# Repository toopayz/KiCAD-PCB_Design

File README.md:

# KiCAD Collection
بِسْمِ اللَّهِ الرَّحْمَنِ الرَّحِيم... 
 
All my KiCAD Collection include Symbol, Footprint, 3D Models, and PCB project.  
Symbol, Footprint, and 3D model can change anytime without information.  
You can refer to "List Component & Board.xlsx" file for reference.

License : Don't Care License, Do what u want...^^...  
Information :
- OS   : Windows 10 64 bit  
- Software : KiCAD v7.0  

## Manage Symbol Libraries  

## Manage Footprint Libraries  

## Manage 3D Model  

//-------------- End Of ReadMe

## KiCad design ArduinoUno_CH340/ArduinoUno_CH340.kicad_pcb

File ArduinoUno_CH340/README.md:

# Arduino Uno R3
بِسْمِ اللَّهِ الرَّحْمَنِ الرَّحِيم... 
 
Create Schematic, PCBA, and 3D Step file based on Arduino Uno R3.  
This project purposes just for trial symbol, footprint, and 3D Model.  

License : Don't Care License, Do what u want...^^...  
Information :
- OS   : Windows 10 64 bit  
- Software : KiCAD v7.0  
- Status : Completed and will Not Continue.
- Date Complete : 20 June 2023

## Project  

## Schematic  

## PCB Board  

## Image  

//-------------- End Of ReadMe

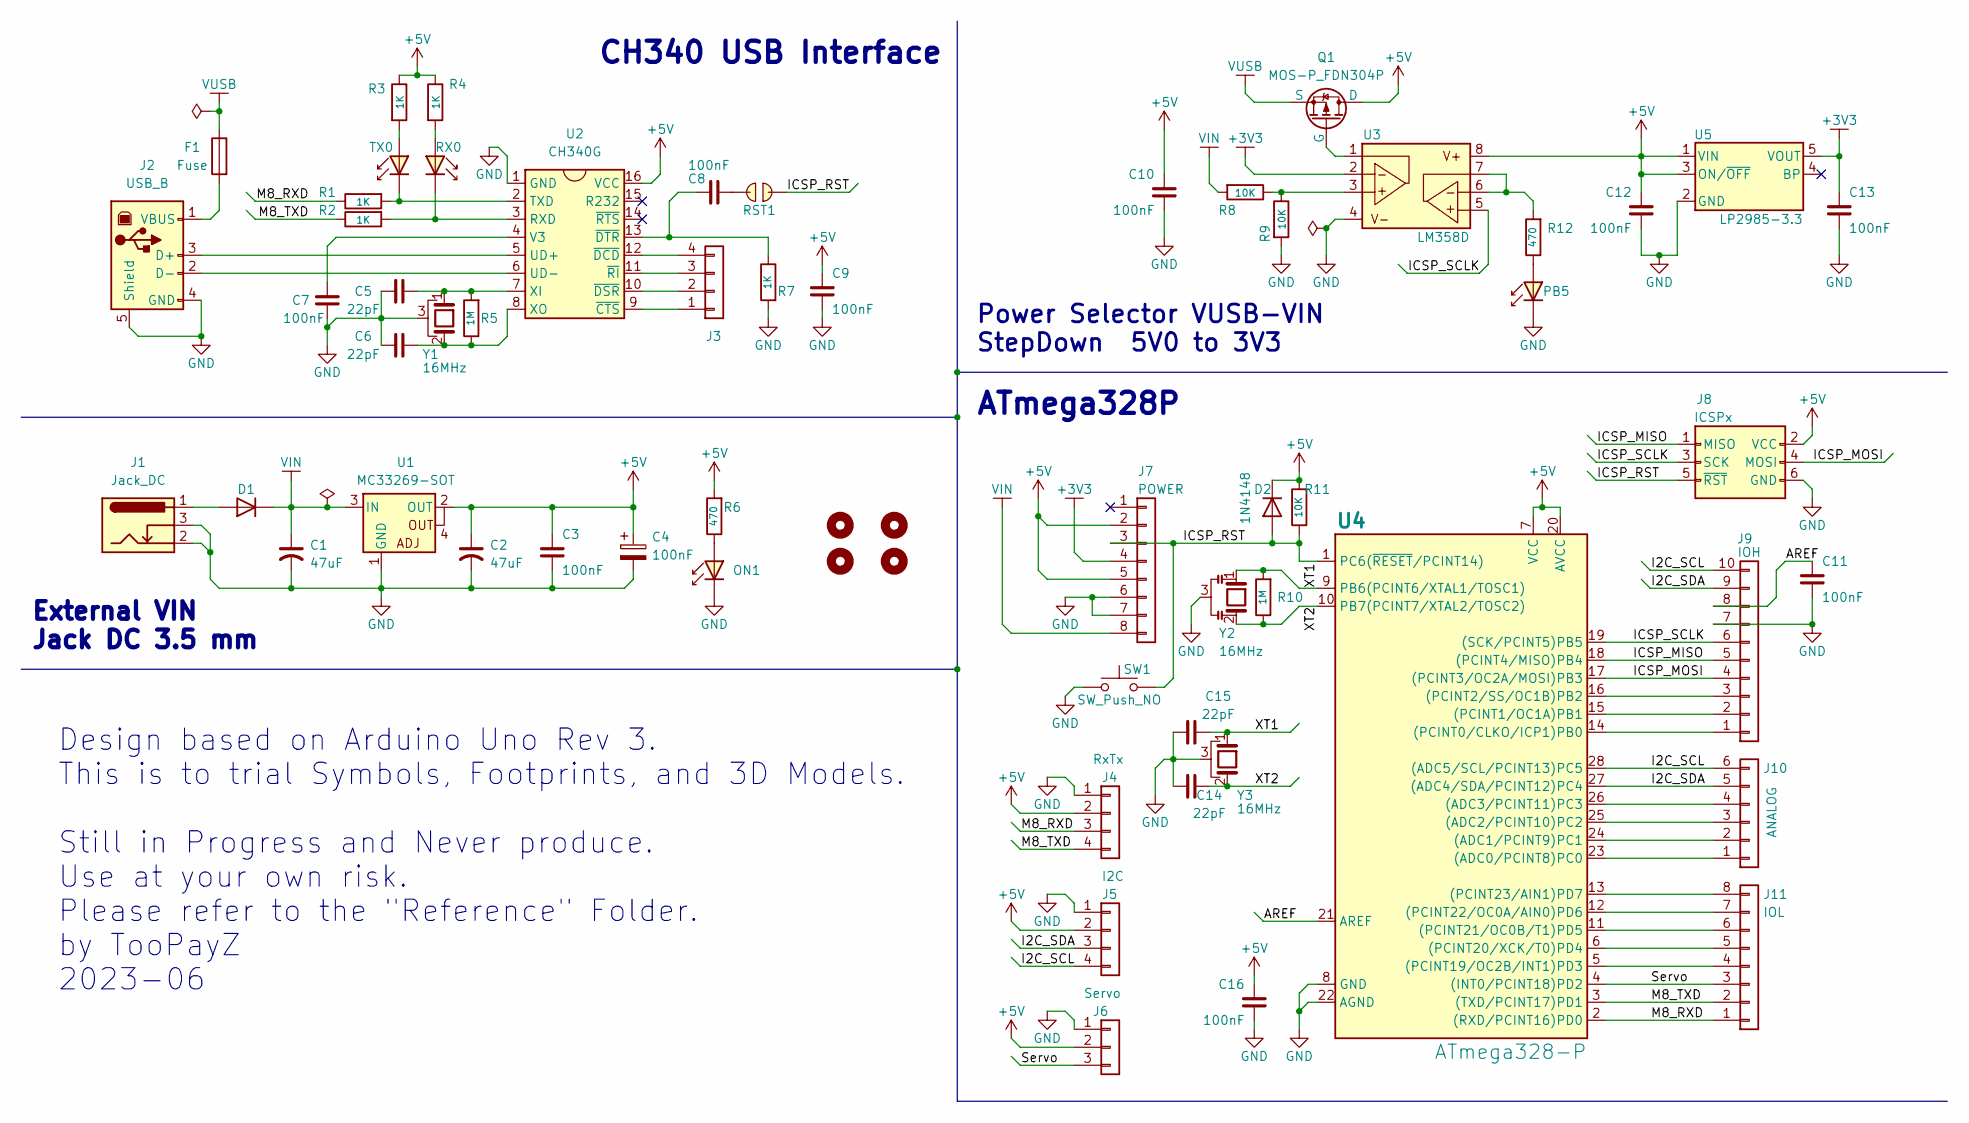
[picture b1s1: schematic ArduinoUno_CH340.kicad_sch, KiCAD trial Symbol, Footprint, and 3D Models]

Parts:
C1, C2: 47uF; C_Radial_D6.3mm_P2.50mm
C3, C7, C8, C9, C10, C11, C12, C13, C16: 100nF; C_0805_HandSolder
C4: 100nF; CP_EIA-3216-10_Kemet-I
C5, C6, C14, C15: 22pF; C_0805_HandSolder
D1: D; D_SMA
D2: 1N4148; D_SOD-123
F1: Fuse; C_1206_HandSolder
H1, H2, H3, H4: MountingHole; MountingHole_3.2mm_M3
J1: Jack_DC; JackDC_Input_3.5mm
J2: USB_B; USB_B_Lumberg_2411_02_Horizontal
J3: Header_4P; PinHeader_1x04_P2.54mm_Vertical
J4: RxTx; PinHeader_1x04_P2.54mm_Vertical
J5: I2C; PinHeader_1x04_P2.54mm_Vertical
J6: Servo; PinHeader_1x03_P2.54mm_Vertical
J7: POWER; PinSocket_1x08_P2.54mm_Vertical
J8: ICSPx; PinHeader_2x03_P2.54mm_Vertical
J9: IOH; PinSocket_1x10_P2.54mm_Vertical
J10: ANALOG; PinSocket_1x06_P2.54mm_Vertical
J11: IOL; PinSocket_1x08_P2.54mm_Vertical
ON1: LRED; LED_0805_HandSolder
PB5: PB5; LED_0805_HandSolder
Q1: MOS-P_FDN304P; SOT-23
R1, R2, R3, R4, R7: 1K; R_0805_HandSolder
R5, R10: 1M; R_0805_HandSolder
R6, R12: 470; R_0805_HandSolder
R8, R9, R11: 10K; R_0805_HandSolder
RST1: RESET_EN; SolderJumper-2_P1.3mm_Open_RoundedPad1.0x1.5mm
RX0: RX; LED_0805_HandSolder
SW1: SW_Push_NO; SW_SPST_CK_RS282G05A3
TX0: TX; LED_0805_HandSolder
U1: MC33269-SOT; SOT-223
U2: CH340G; SOIC-16_3.9x9.9mm_P1.27mm
U3: LM358D; SOIC-8_3.9x4.9mm_P1.27mm
U4: ATmega328-P; DIP-28_W7.62mm
U5: LP2985-3.3; SOT-23-5
Y1, Y3: 16MHz; Crystal_HC49-4H_Vertical_GND
Y2: 16MHz; Resonator_SMD_Murata_CSTxExxV-3Pin_3.0x1.1mm_HandSoldering

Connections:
+3V3: C13.1, J7.4, U3.2 (INPA-), U5.5 (VOUT)
+5V: C2.1, C3.1, C4.1, C9.1, C10.1, C12.1, C16.1, D2.1 (K), J4.2, J5.2, J6.2, J7.2, J7.5, J8.2 (VCC), Q1.1 (D), R3.2, R4.2, R6.1, R11.1, U1.2 (OUT), U1.4 (OUT), U2.16 (VCC), U3.8 (V+), U4.7 (VCC), U4.20 (AVCC), U5.1 (VIN), U5.3 (ON/~OFF)
/AREF: C11.1, J9.8, U4.21 (AREF)
/I2C_SCL: J5.4, J9.10, J10.6, U4.28 ((ADC5/SCL/PCINT13)PC5)
/I2C_SDA: J5.3, J9.9, J10.5, U4.27 ((ADC4/SDA/PCINT12)PC4)
/ICSP_MISO: J8.1 (MISO), J9.5, U4.18 ((PCINT4/MISO)PB4)
/ICSP_MOSI: J8.4 (MOSI), J9.4, U4.17 ((PCINT3/OC2A/MOSI)PB3)
/ICSP_RST: D2.2 (A), J7.3, J8.5 (~RST), R11.2, RST1.1, SW1.2, U4.1 (PC6(~RESET/PCINT14)); also elsewhere on the board
/ICSP_SCLK: J8.3 (SCK), J9.6, U3.5 (INPB-), U4.19 ((SCK/PCINT5)PB5)
/M8_RXD: J4.3, J11.1, R1.2, U4.2 ((RXD/PCINT16)PD0)
/M8_TXD: J4.4, J11.2, R2.2, U4.3 ((TXD/PCINT17)PD1)
/Servo: J6.3, J11.3, U4.4 ((INT0/PCINT18)PD2)
/XT1: C15.2, R10.1, U4.9 (PB6(PCINT6/XTAL1/TOSC1)), Y2.1, Y3.1
/XT2: C14.2, R10.2, U4.10 (PB7(PCINT7/XTAL2/TOSC2)), Y2.2, Y3.2
GND: C1.2, C2.2, C3.2, C4.2, C5.1, C6.1, C7.2, C9.2, C10.2, C11.2, C12.2, C13.2, C14.1, C15.1, C16.2, J1.2, J1.3, J2.4 (GND), J2.5 (Shield), J4.1, J5.1, J6.1, J7.6, J7.7, J8.6 (GND), J9.7, ON1.1 (K), PB5.1 (K), R7.1, R9.1, SW1.1, U1.1 (GND), U2.1 (GND), U3.4 (V-), U4.8 (GND), U4.22 (AGND), U5.2 (GND), Y1.3, Y2.3, Y3.3; also elsewhere on the board
unnamed: C8.1, RST1.2
unnamed: D1.2 (A), J1.1
unnamed: J2.3 (D+), U2.5 (UD+)
unnamed: J2.2 (D-), U2.6 (UD-)
unnamed: F1.1, J2.1 (VBUS)
unnamed: J3.1, U2.9 (~CTS)
unnamed: J3.2, U2.10 (~DSR)
unnamed: J3.3, U2.11 (~RI)
unnamed: J3.4, U2.12 (~DCD)
unnamed: J9.1, U4.14 ((PCINT0/CLKO/ICP1)PB0)
unnamed: J9.2, U4.15 ((PCINT1/OC1A)PB1)
unnamed: J9.3, U4.16 ((PCINT2/SS/OC1B)PB2)
unnamed: J10.1, U4.23 ((ADC0/PCINT8)PC0)
unnamed: J10.2, U4.24 ((ADC1/PCINT9)PC1)
unnamed: J10.3, U4.25 ((ADC2/PCINT10)PC2)
unnamed: J10.4, U4.26 ((ADC3/PCINT11)PC3)
unnamed: J11.4, U4.5 ((PCINT19/OC2B/INT1)PD3)
unnamed: J11.5, U4.6 ((PCINT20/XCK/T0)PD4)
unnamed: J11.6, U4.11 ((PCINT21/OC0B/T1)PD5)
unnamed: J11.7, U4.12 ((PCINT22/OC0A/AIN0)PD6)
unnamed: J11.8, U4.13 ((PCINT23/AIN1)PD7)
unnamed: ON1.2 (A), R6.2
unnamed: PB5.2 (A), R12.2
unnamed: Q1.2 (G), U3.1 (OUTA)
unnamed: R4.1, RX0.2 (A)
unnamed: R2.1, RX0.1 (K), U2.3 (RXD)
unnamed: R3.1, TX0.2 (A)
unnamed: R1.1, TX0.1 (K), U2.2 (TXD)
unnamed: C7.1, U2.4 (V3)
unnamed: C5.2, R5.1, U2.7 (XI), Y1.1
unnamed: C6.2, R5.2, U2.8 (XO), Y1.2
unnamed: C8.2, R7.2, U2.13 (~DTR)
unnamed: R8.2, R9.2, U3.3 (INPA+)
unnamed: R12.1, U3.6 (INPB+), U3.7 (OUTB)
VIN: C1.1, D1.1 (K), J7.8, R8.1, U1.3 (IN)
VUSB: F1.2, Q1.3 (S)

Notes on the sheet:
Power Selector VUSB-VIN StepDown 5V0 to 3V3
Design based on Arduino Uno Rev 3. This is to trial Symbols, Footprints, and 3D Models. Still in Progress and Never produce. Use at your own risk. Please refer to the "Reference" Folder. by TooPayZ 2023-06
CH340 USB Interface
ATmega328P
External VIN Jack DC 3.5 mm

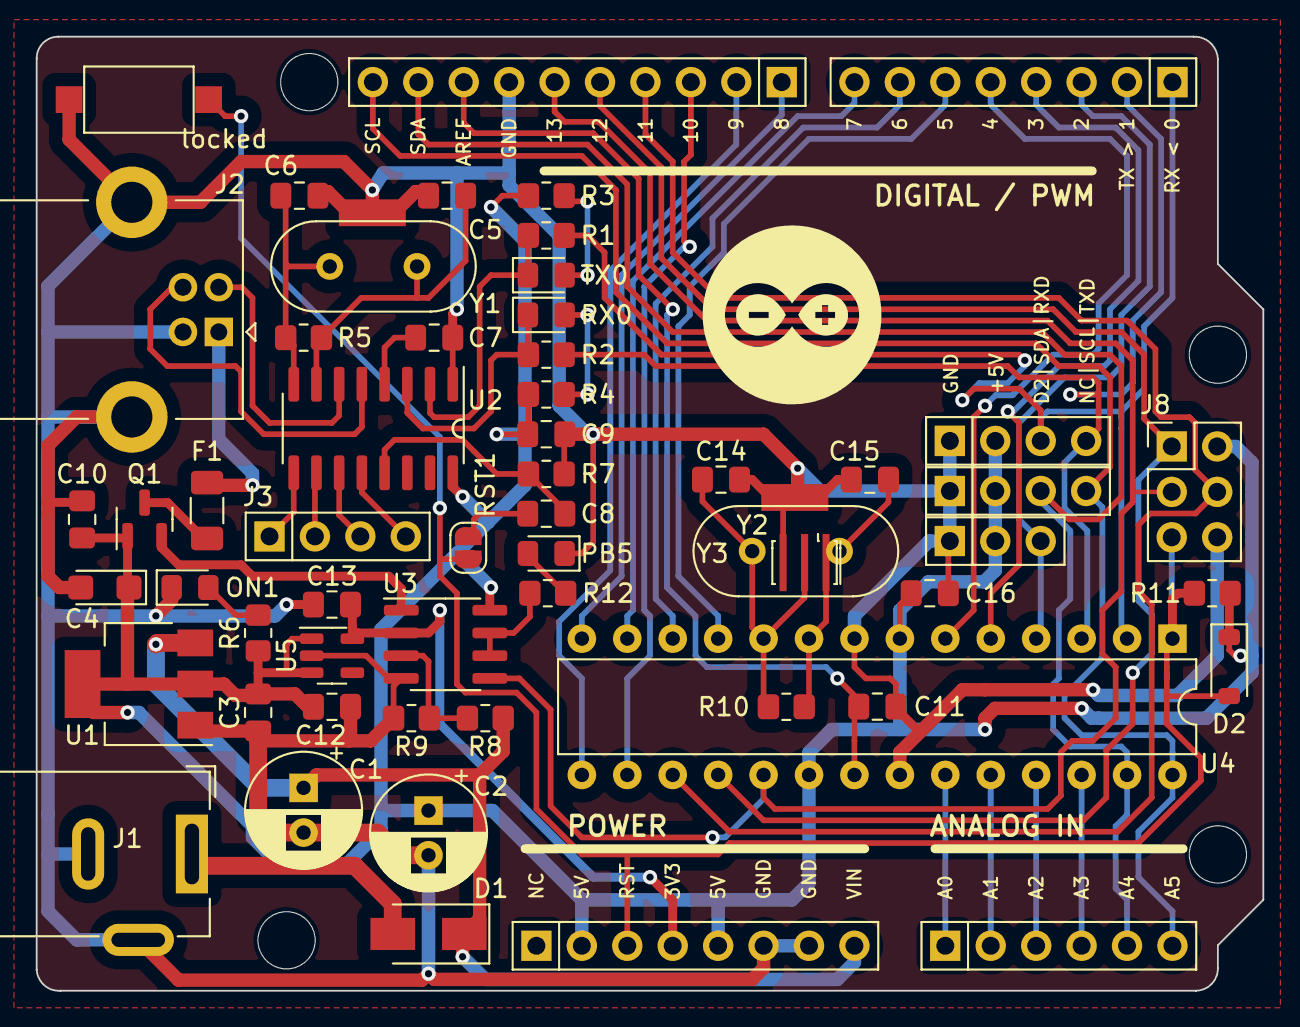
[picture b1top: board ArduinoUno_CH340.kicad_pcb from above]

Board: 2 copper layers, 68.6 x 53.3 mm, 61 parts (0 on the bottom side), 51 nets.

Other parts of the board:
locked: SW_Push_NO; SW_SPST_CK_RS282G05A3

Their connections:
/ICSP_RST: locked.2; also elsewhere on the board
GND: locked.1; also elsewhere on the board

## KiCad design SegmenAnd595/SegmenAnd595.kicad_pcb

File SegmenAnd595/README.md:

# Display 7 Segmen with 595
بِسْمِ اللَّهِ الرَّحْمَنِ الرَّحِيم... 
 
Create Schematic, PCBA, and 3D Step file for 7 Segmen Display + 74HC595.  
This project purposes just for trial symbol, footprint, and 3D Model.  

License : Don't Care License, Do what u want...^^...  
Information :
- OS   : Windows 10 64 bit  
- Software : KiCAD v7.0  
- Status : Completed and will Not Continue.
- Date Complete : 20 June 2023

## Project  

## Schematic  

## PCB Board  

## Image 01  

## Image 02  

//-------------- End Of ReadMe

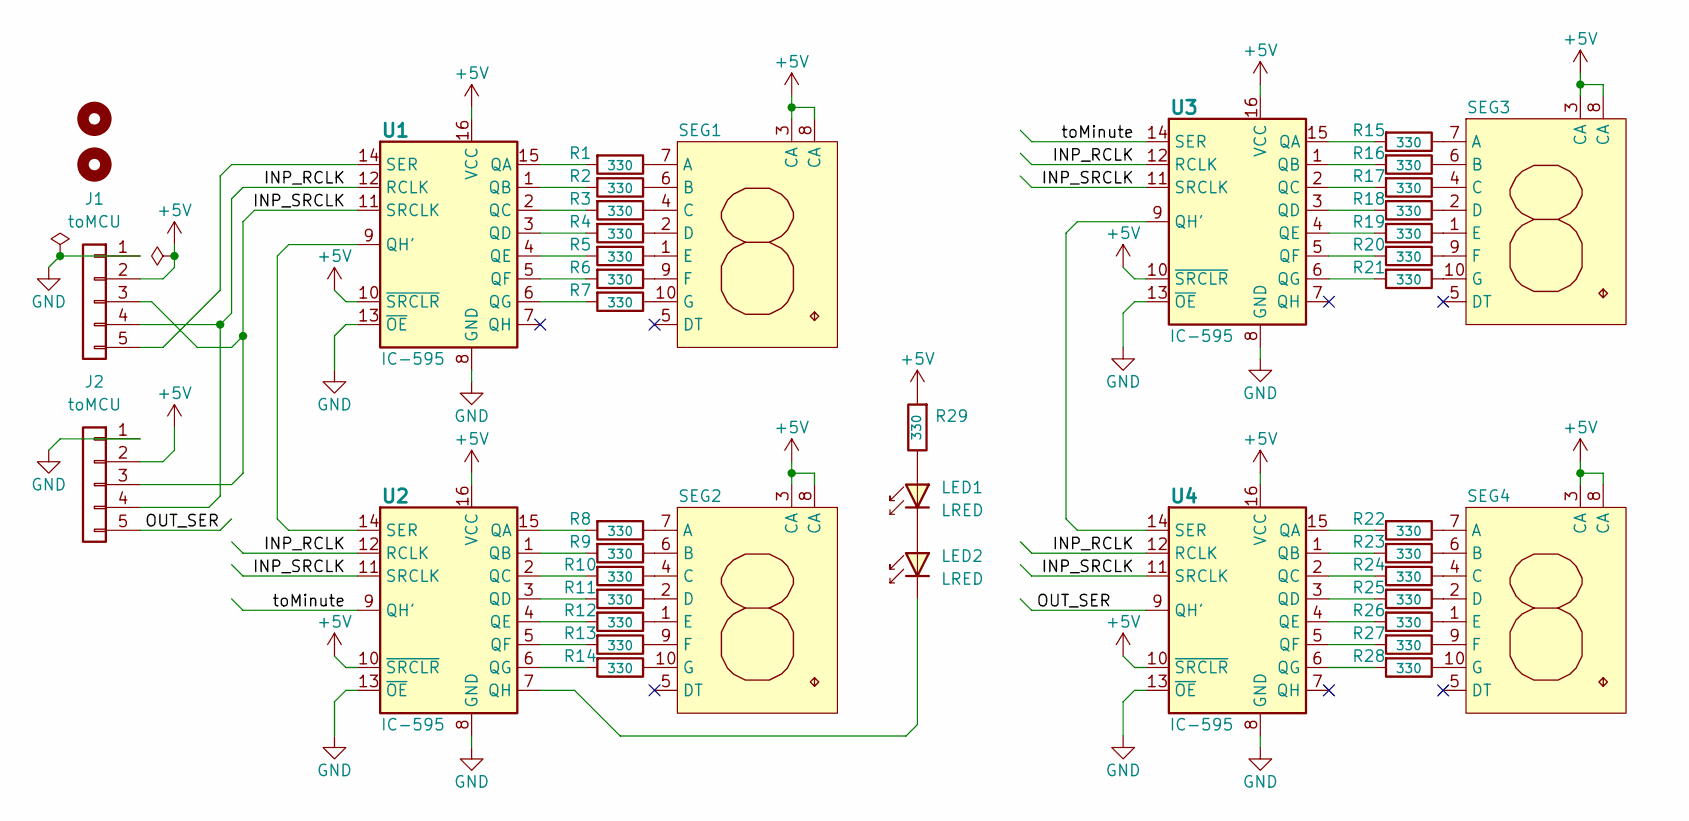
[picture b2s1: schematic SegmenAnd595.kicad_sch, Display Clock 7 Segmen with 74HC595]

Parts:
H1, H2: Screw; MountingHole_3.2mm_M3_Pad
J1, J2: toMCU; JST_XH_B5B-XH-A_1x05_P2.50mm_Vertical
LED1, LED2: LRED; LED_D3.0mm_RED
R1: 330; R_0603_HandSolder
R2, R3, R4, R5, R6, R7, R8, R9, R10, R11, R12, R13, R14, R15, R16, R17, R18, R19, R20, R21, R22, R23, R24, R25, R26, R27, R28, R29: 330; R_0805_HandSolder
SEG1, SEG2, SEG3, SEG4: Segmen-CA
U1, U2, U3, U4: IC-595; SOP-16_4.4x10.4mm_P1.27mm

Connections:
+5V: J1.2, J2.2, R29.1, SEG1.3 (CA), SEG1.8 (CA), SEG2.3 (CA), SEG2.8 (CA), SEG3.3 (CA), SEG3.8 (CA), SEG4.3 (CA), SEG4.8 (CA), U1.10 (~SRCLR), U1.16 (VCC), U2.10 (~SRCLR), U2.16 (VCC), U3.10 (~SRCLR), U3.16 (VCC), U4.10 (~SRCLR), U4.16 (VCC)
/INP_RCLK: J1.4, J2.4, U1.12 (RCLK), U2.12 (RCLK), U3.12 (RCLK), U4.12 (RCLK)
/INP_SRCLK: J1.3, J2.3, U1.11 (SRCLK), U2.11 (SRCLK), U3.11 (SRCLK), U4.11 (SRCLK)
/OUT_SER: J2.5, U4.9 (QH')
/toMinute: U2.9 (QH'), U3.14 (SER)
GND: J1.1, J2.1, U1.8 (GND), U1.13 (~OE), U2.8 (GND), U2.13 (~OE), U3.8 (GND), U3.13 (~OE), U4.8 (GND), U4.13 (~OE)
unnamed: J1.5, U1.14 (SER)
unnamed: LED1.2 (A), R29.2
unnamed: LED1.1 (K), LED2.2 (A)
unnamed: LED2.1 (K), U2.7 (QH)
unnamed: R1.2, SEG1.7 (A)
unnamed: R2.2, SEG1.6 (B)
unnamed: R3.2, SEG1.4 (C)
unnamed: R4.2, SEG1.2 (D)
unnamed: R5.2, SEG1.1 (E)
unnamed: R6.2, SEG1.9 (F)
unnamed: R7.2, SEG1.10 (G)
unnamed: R8.2, SEG2.7 (A)
unnamed: R9.2, SEG2.6 (B)
unnamed: R10.2, SEG2.4 (C)
unnamed: R11.2, SEG2.2 (D)
unnamed: R12.2, SEG2.1 (E)
unnamed: R13.2, SEG2.9 (F)
unnamed: R14.2, SEG2.10 (G)
unnamed: R15.2, SEG3.7 (A)
unnamed: R16.2, SEG3.6 (B)
unnamed: R17.2, SEG3.4 (C)
unnamed: R18.2, SEG3.2 (D)
unnamed: R19.2, SEG3.1 (E)
unnamed: R20.2, SEG3.9 (F)
unnamed: R21.2, SEG3.10 (G)
unnamed: R22.2, SEG4.7 (A)
unnamed: R23.2, SEG4.6 (B)
unnamed: R24.2, SEG4.4 (C)
unnamed: R25.2, SEG4.2 (D)
unnamed: R26.2, SEG4.1 (E)
unnamed: R27.2, SEG4.9 (F)
unnamed: R28.2, SEG4.10 (G)
unnamed: R1.1, U1.15 (QA)
unnamed: R2.1, U1.1 (QB)
unnamed: R3.1, U1.2 (QC)
unnamed: R4.1, U1.3 (QD)
unnamed: R5.1, U1.4 (QE)
unnamed: R6.1, U1.5 (QF)
unnamed: R7.1, U1.6 (QG)
unnamed: U1.9 (QH'), U2.14 (SER)
unnamed: R8.1, U2.15 (QA)
unnamed: R9.1, U2.1 (QB)
unnamed: R10.1, U2.2 (QC)
unnamed: R11.1, U2.3 (QD)
unnamed: R12.1, U2.4 (QE)
unnamed: R13.1, U2.5 (QF)
unnamed: R14.1, U2.6 (QG)
unnamed: R15.1, U3.15 (QA)
unnamed: R16.1, U3.1 (QB)
unnamed: R17.1, U3.2 (QC)
unnamed: R18.1, U3.3 (QD)
unnamed: R19.1, U3.4 (QE)
unnamed: R20.1, U3.5 (QF)
unnamed: R21.1, U3.6 (QG)
unnamed: U3.9 (QH'), U4.14 (SER)
unnamed: R22.1, U4.15 (QA)
unnamed: R23.1, U4.1 (QB)
unnamed: R24.1, U4.2 (QC)
unnamed: R25.1, U4.3 (QD)
unnamed: R26.1, U4.4 (QE)
unnamed: R27.1, U4.5 (QF)
unnamed: R28.1, U4.6 (QG)

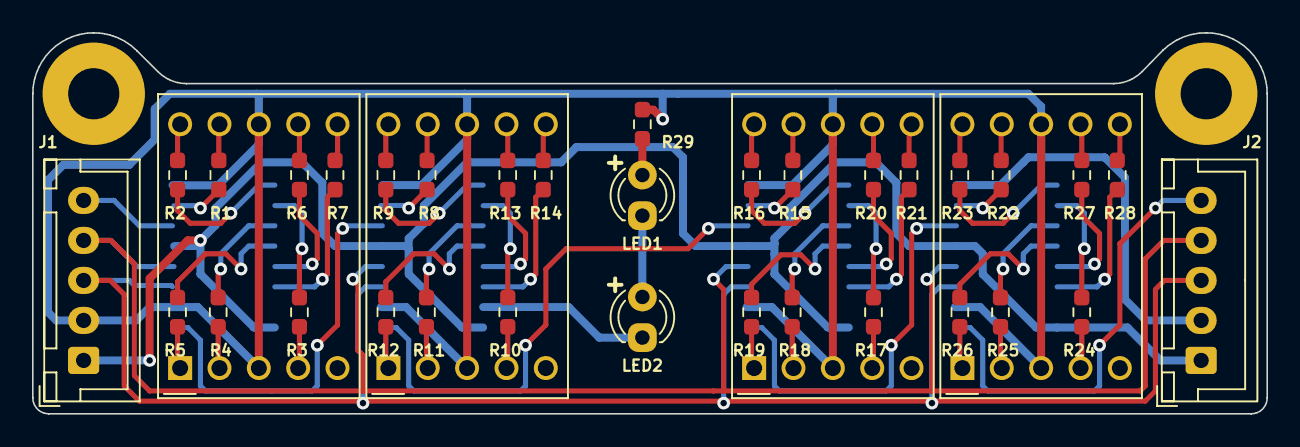
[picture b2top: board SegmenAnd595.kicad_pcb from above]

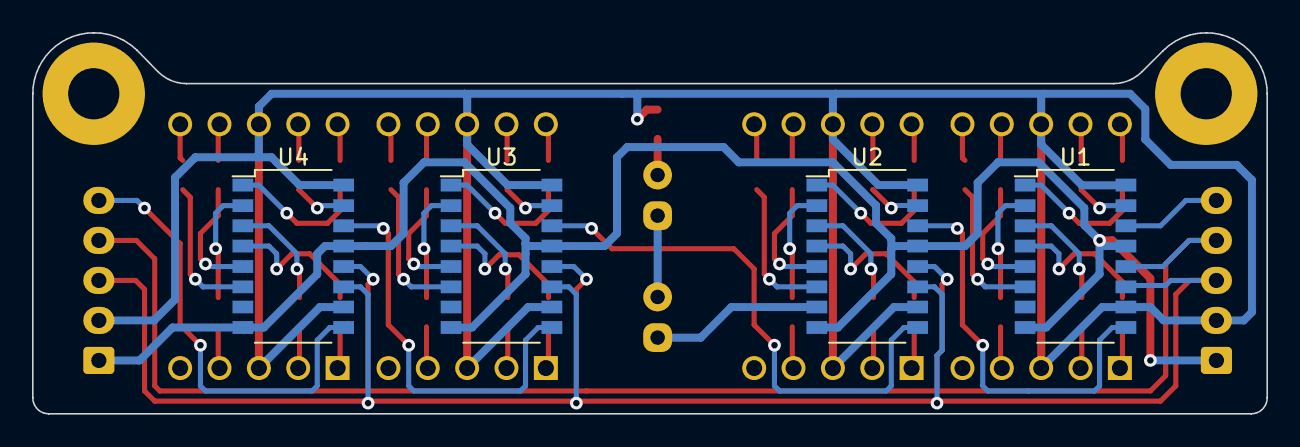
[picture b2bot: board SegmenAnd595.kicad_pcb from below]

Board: 2 copper layers, 77.2 x 23.8 mm, 43 parts (4 on the bottom side), 68 nets.

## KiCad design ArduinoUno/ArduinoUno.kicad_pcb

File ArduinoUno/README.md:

# Arduino Uno
بِسْمِ اللَّهِ الرَّحْمَنِ الرَّحِيم... 
 
Only trial for Symbol and footprint.  
PCB Board will not continue.  
Thank you.  

//-------------- End Of ReadMe

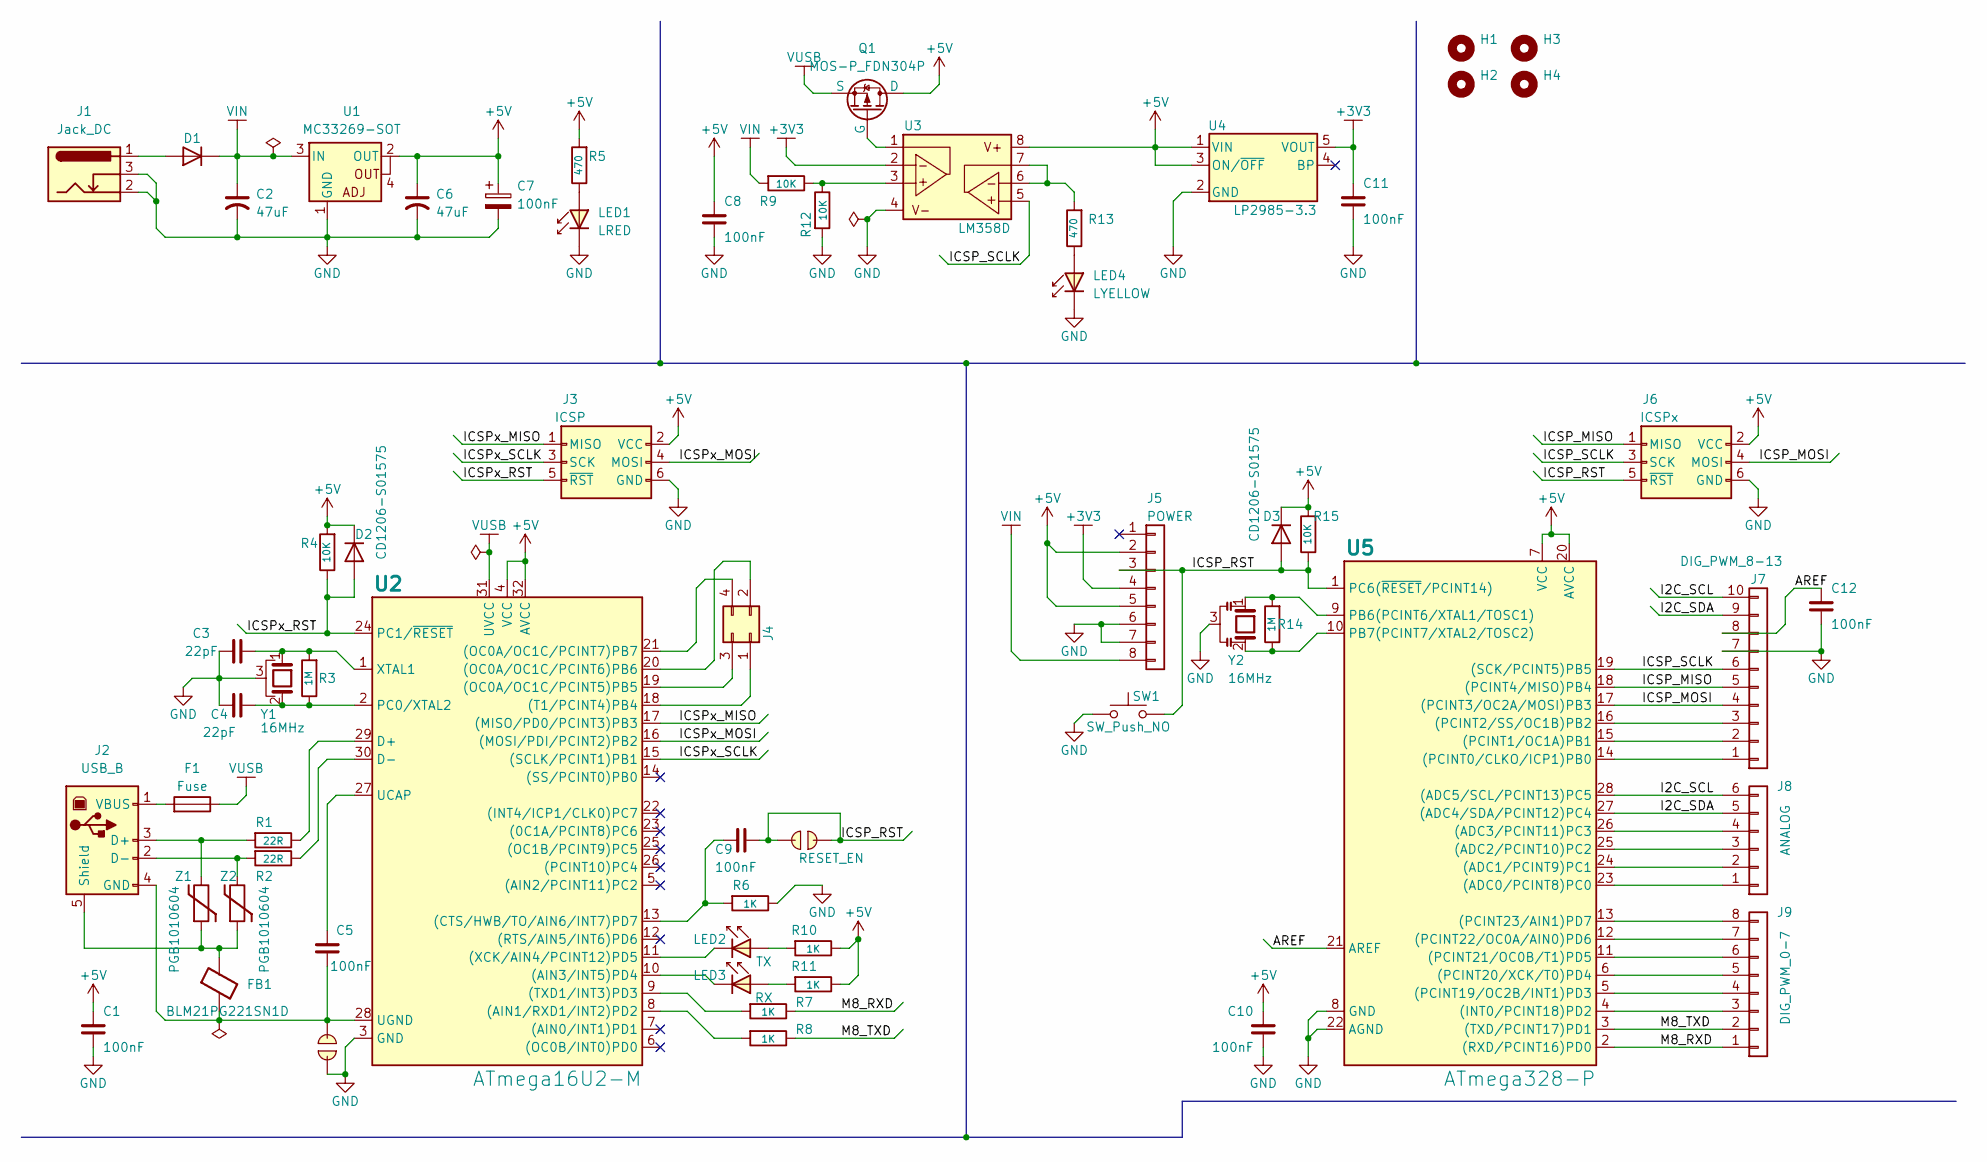
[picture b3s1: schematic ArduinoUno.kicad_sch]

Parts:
C1, C5, C8, C9, C10, C11, C12: 100nF; C_0805_HandSolder
C2, C6: 47uF; C_Radial_D4.0mm_H5.0mm_P1.50mm
C3, C4: 22pF; C_0805_HandSolder
C7: 100nF; CP_EIA-3216-10_Kemet-I
D1: D; D_SMA
D2, D3: CD1206-S01575; D_1206_HandSolder
F1: Fuse; C_1206_HandSolder
FB1: BLM21PG221SN1D; R_0603_HandSolder
H1, H2, H3, H4: MountingHole; MountingHole_3.2mm_M3
J1: Jack_DC; JackDC_Input_3.5mm
J2: USB_B; USB_B_Lumberg_2411_02_Horizontal
J3: ICSP; PinHeader_2x03_P2.54mm_Vertical
J4: Conn_02x02; PinHeader_2x02_P2.54mm_Vertical
J5: POWER; PinSocket_1x08_P2.54mm_Vertical
J6: ICSPx; PinHeader_2x03_P2.54mm_Vertical
J7: DIG_PWM_8-13; PinSocket_1x10_P2.54mm_Vertical
J8: ANALOG; PinSocket_1x06_P2.54mm_Vertical
J9: DIG_PWM_0-7; PinSocket_1x08_P2.54mm_Vertical
LED1: LRED; D_0805_HandSolder
LED2: TX; D_0805_HandSolder
LED3: RX; D_0805_HandSolder
LED4: LYELLOW; D_0805_HandSolder
Q1: MOS-P_FDN304P; SOT-23
R1, R2: 22R; R_0805_HandSolder
R3, R14: 1M; R_0805_HandSolder
R4, R9, R12, R15: 10K; R_0805_HandSolder
R5, R13: 470; R_0805_HandSolder
R6, R7, R8, R10, R11: 1K; R_0805_HandSolder
SOL1: SolderJumper-2_P1.3mm_Open_RoundedPad1.0x1.5mm
SOL2: RESET_EN; SolderJumper-2_P1.3mm_Open_RoundedPad1.0x1.5mm
SW1: SW_Push_NO; SW_SPST_CK_RS282G05A3
U1: MC33269-SOT; SOT-223
U2: ATmega16U2-M; QFN-32-1EP_5x5mm_P0.5mm_EP3.1x3.1mm
U3: LM358D; SOIC-8_3.9x4.9mm_P1.27mm
U4: LP2985-3.3; SOT-23-5
U5: ATmega328-P; DIP-28_W7.62mm
Y1: 16MHz; Crystal_HC49-4H_Vertical_GND
Y2: 16MHz; Resonator_SMD_Murata_CSTxExxV-3Pin_3.0x1.1mm_HandSoldering
Z1, Z2: PGB1010604; C_0603_HandSolder

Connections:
+3V3: C11.1, J5.4, U3.2 (INPA-), U4.5 (VOUT)
+5V: C1.1, C6.1, C7.1, C8.1, C10.1, D2.1 (K), D3.1 (K), J3.2 (VCC), J5.2, J5.5, J6.2 (VCC), Q1.1 (D), R4.1, R5.1, R10.2, R11.2, R15.1, U1.2 (OUT), U1.4 (OUT), U2.4 (VCC), U2.32 (AVCC), U3.8 (V+), U4.1 (VIN), U4.3 (ON/~OFF), U5.7 (VCC), U5.20 (AVCC)
/AREF: C12.1, J7.8, U5.21 (AREF)
/I2C_SCL: J7.10, J8.6, U5.28 ((ADC5/SCL/PCINT13)PC5)
/I2C_SDA: J7.9, J8.5, U5.27 ((ADC4/SDA/PCINT12)PC4)
/ICSP_MISO: J6.1 (MISO), J7.5, U5.18 ((PCINT4/MISO)PB4)
/ICSP_MOSI: J6.4 (MOSI), J7.4, U5.17 ((PCINT3/OC2A/MOSI)PB3)
/ICSP_RST: C9.1, D3.2 (A), J5.3, J6.5 (~RST), R15.2, SOL2.1, SOL2.2, SW1.2, U5.1 (PC6(~RESET/PCINT14)); also elsewhere on the board
/ICSP_SCLK: J6.3 (SCK), J7.6, U3.5 (INPB-), U5.19 ((SCK/PCINT5)PB5)
/ICSPx_MISO: J3.1 (MISO), U2.17 ((MISO/PD0/PCINT3)PB3)
/ICSPx_MOSI: J3.4 (MOSI), U2.16 ((MOSI/PDI/PCINT2)PB2)
/ICSPx_RST: D2.2 (A), J3.5 (~RST), R4.2, U2.24 (PC1/~RESET)
/ICSPx_SCLK: J3.3 (SCK), U2.15 ((SCLK/PCINT1)PB1)
/M8_RXD: J9.1, R7.2, U5.2 ((RXD/PCINT16)PD0)
/M8_TXD: J9.2, R8.2, U5.3 ((TXD/PCINT17)PD1)
GND: C1.2, C2.2, C3.1, C4.1, C6.2, C7.2, C8.2, C10.2, C11.2, C12.2, J1.2, J1.3, J3.6 (GND), J5.6, J5.7, J6.6 (GND), J7.7, LED1.1 (K), LED4.1 (K), R6.2, R12.1, SOL1.1, SW1.1, U1.1 (GND), U2.3 (GND), U2.33 (GND), U3.4 (V-), U4.2 (GND), U5.8 (GND), U5.22 (AGND), Y1.3, Y2.3; also elsewhere on the board
unnamed: D1.2 (A), J1.1
unnamed: J2.3 (D+), R1.1, Z1.1
unnamed: J2.2 (D-), R2.1, Z2.1
unnamed: C5.2, FB1.2, J2.4 (GND), SOL1.2, U2.28 (UGND)
unnamed: FB1.1, J2.5 (Shield), Z1.2, Z2.2
unnamed: F1.1, J2.1 (VBUS)
unnamed: J4.1, U2.18 ((T1/PCINT4)PB4)
unnamed: J4.2, U2.20 ((OC0A/OC1C/PCINT6)PB6)
unnamed: J4.3, U2.19 ((OC0A/OC1C/PCINT5)PB5)
unnamed: J4.4, U2.21 ((OC0A/OC1C/PCINT7)PB7)
unnamed: J7.1, U5.14 ((PCINT0/CLKO/ICP1)PB0)
unnamed: J7.2, U5.15 ((PCINT1/OC1A)PB1)
unnamed: J7.3, U5.16 ((PCINT2/SS/OC1B)PB2)
unnamed: J8.1, U5.23 ((ADC0/PCINT8)PC0)
unnamed: J8.2, U5.24 ((ADC1/PCINT9)PC1)
unnamed: J8.3, U5.25 ((ADC2/PCINT10)PC2)
unnamed: J8.4, U5.26 ((ADC3/PCINT11)PC3)
unnamed: J9.3, U5.4 ((INT0/PCINT18)PD2)
unnamed: J9.4, U5.5 ((PCINT19/OC2B/INT1)PD3)
unnamed: J9.5, U5.6 ((PCINT20/XCK/T0)PD4)
unnamed: J9.6, U5.11 ((PCINT21/OC0B/T1)PD5)
unnamed: J9.7, U5.12 ((PCINT22/OC0A/AIN0)PD6)
unnamed: J9.8, U5.13 ((PCINT23/AIN1)PD7)
unnamed: LED1.2 (A), R5.2
unnamed: LED2.2 (A), R10.1
unnamed: LED2.1 (K), U2.11 ((XCK/AIN4/PCINT12)PD5)
unnamed: LED3.2 (A), R11.1
unnamed: LED3.1 (K), U2.10 ((AIN3/INT5)PD4)
unnamed: LED4.2 (A), R13.2
unnamed: Q1.2 (G), U3.1 (OUTA)
unnamed: R8.1, U2.8 ((AIN1/RXD1/INT2)PD2)
unnamed: C9.2, R6.1, U2.13 ((CTS/HWB/TO/AIN6/INT7)PD7)
unnamed: R7.1, U2.9 ((TXD1/INT3)PD3)
unnamed: R1.2, U2.29 (D+)
unnamed: R2.2, U2.30 (D-)
unnamed: C4.2, R3.2, U2.2 (PC0/XTAL2), Y1.2
unnamed: C5.1, U2.27 (UCAP)
unnamed: C3.2, R3.1, U2.1 (XTAL1), Y1.1
unnamed: R9.2, R12.2, U3.3 (INPA+)
unnamed: R13.1, U3.6 (INPB+), U3.7 (OUTB)
unnamed: R14.1, U5.9 (PB6(PCINT6/XTAL1/TOSC1)), Y2.1
unnamed: R14.2, U5.10 (PB7(PCINT7/XTAL2/TOSC2)), Y2.2
VIN: C2.1, D1.1 (K), J5.8, R9.1, U1.3 (IN)
VUSB: F1.2, Q1.3 (S), U2.31 (UVCC)

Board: 2 copper layers, 62 parts (0 on the bottom side), 60 nets, no tracks yet.

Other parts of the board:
locked: SW_Push_NO; SW_SPST_CK_RS282G05A3

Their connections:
/ICSP_RST: locked.2; also elsewhere on the board
GND: locked.1; also elsewhere on the board

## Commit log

2022-07-22 KiCAD Collection
    بِسْمِ اللَّهِ الرَّحْمَنِ الرَّحِيم...
    All my Collection of Symbol, Footprint, 3D models, and PCB KiCAD Project.
    Coming soon tutorial and others.
    Hopefully it come true.
    License : Don't Care License, Do what u want...
    Enjoy it...^^...
2022-07-22 Fist Commit
2023-06-03 Add 3D Slide Switch
2023-06-09 Major Update
    Change structure for Symbol and Footprint
2023-06-14 Major Update Symbol
    Major change focus for Symbol.
    Almost all is change for folder structure and library.
2023-06-16 Arduino CH340
    Change footprint, 3D model etc
2023-06-16 KiCAD Picture
    Create New Folder "KiCAD Picture"
2023-06-16 Update KiCAD_Picture Folder Name
2023-06-16 Chamge BMP to PNG
2023-06-19 Complete Arduino Uno CH340
    Complete Project Arduino uno CH340
2023-06-19 Update Readme Arduino Uno
    Update Readme Note for Arduino Uno Project.
2023-06-30 Complete Segmen595
    Create New trial project for 7 Segmen + HC595
2025-02-27 2025 start update
2025-02-28 Update 3D part 2025
2025-03-03 Check update for 2025
2025-03-07 Major change
2025-06-10 Add Connector 3D
